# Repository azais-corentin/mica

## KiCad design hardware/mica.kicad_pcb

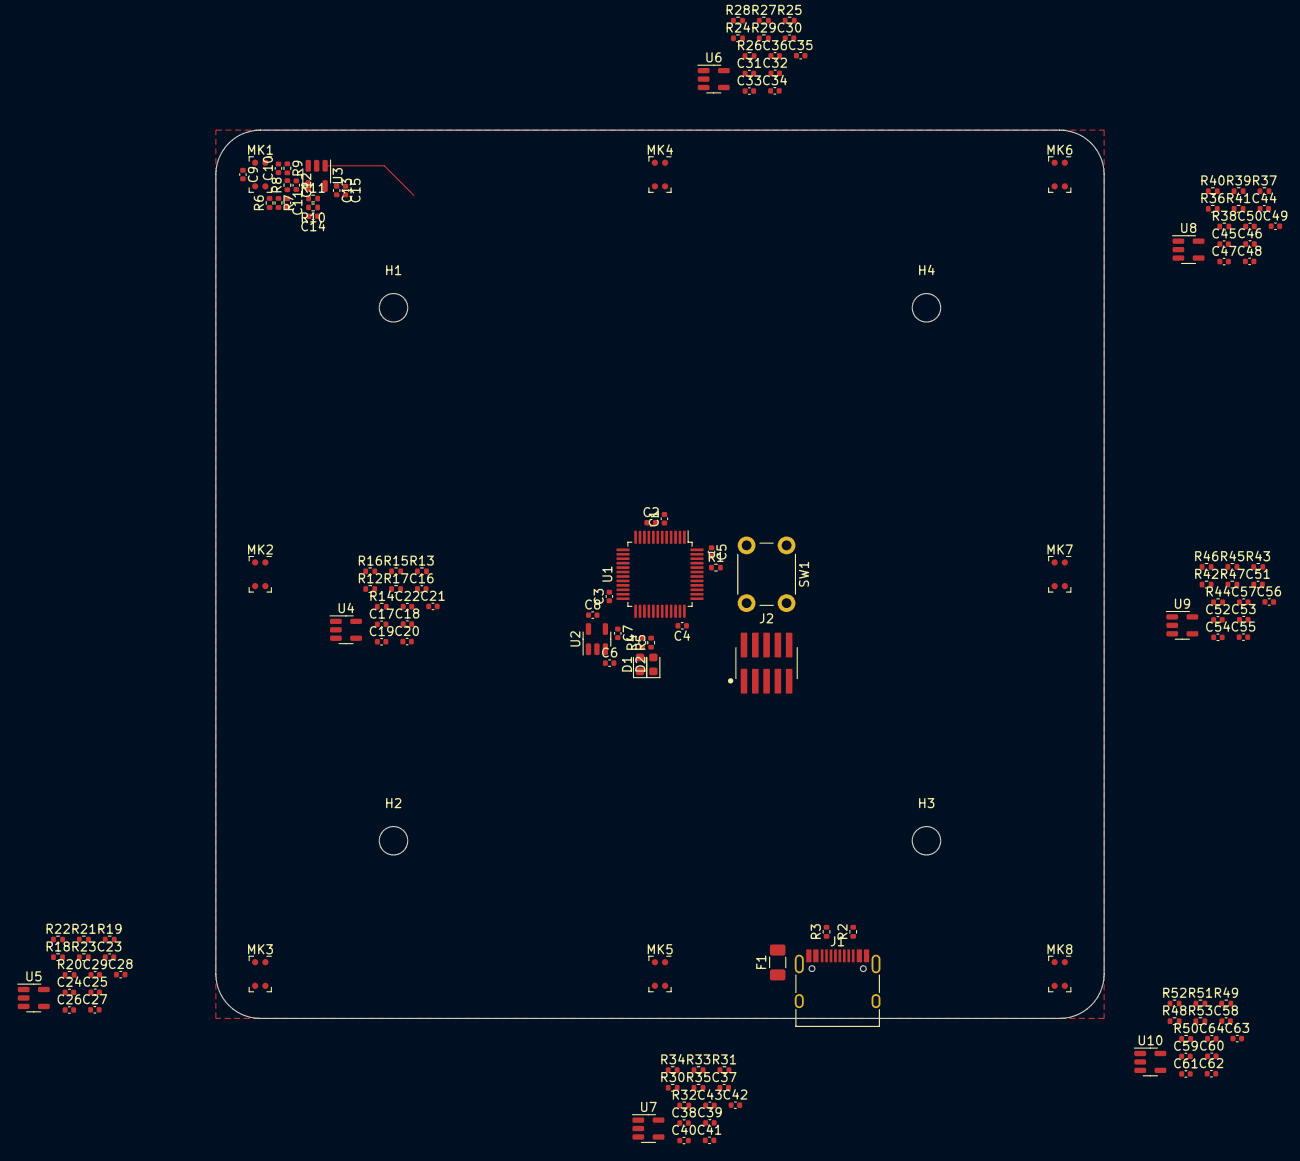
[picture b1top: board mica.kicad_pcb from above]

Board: 2 copper layers, 100.0 x 100.0 mm, 145 parts (0 on the bottom side), 74 nets.

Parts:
C1, C2, C3, C4, C5, C9, C15, C16, C22, C23, C29, C30, C36, C37, C43, C44, C50, C51, C57, C58, C64: 100n; C_0402_1005Metric
C6, C8, C14, C21, C28, C35, C42, C49, C56, C63: 2.2u; C_0402_1005Metric
C7: 470p; C_0402_1005Metric
C10, C17, C24, C31, C38, C45, C52, C59: 1u; C_0402_1005Metric
C11, C12, C18, C19, C25, C26, C32, C33, C39, C40, C46, C47, C53, C54, C60, C61: 47n; C_0402_1005Metric
C13, C20, C27, C34, C41, C48, C55, C62: 10n; C_0402_1005Metric
D1: LED_Red; LED_0603_1608Metric
D2: LED_Green; LED_0603_1608Metric
F1: Polyfuse_Small; Fuse_1206_3216Metric
H1, H2, H3, H4: MountingHole; MountingHole_3.2mm_M3
J1: USB_C_Receptacle_USB2.0; USB_C_Receptacle_HRO_TYPE-C-31-M-12
J2: Conn_ARM_JTAG_SWD_10; Samtec_FTSH-105-01-L-DV-K
MK1, MK2, MK3, MK4, MK5, MK6, MK7, MK8: AP3722AT; AllPower_AP3722AT_3.76x2.24mm
R1: 10k; R_0402_1005Metric
R2, R3: 5.1k; R_0402_1005Metric
R4, R5: 470; R_0402_1005Metric
R6, R7, R8, R12, R13, R14, R18, R19, R20, R24, R25, R26, R30, R31, R32, R36, R37, R38, R42, R43, R44, R48, R49, R50: 1M; R_0402_1005Metric
R9, R15, R21, R27, R33, R39, R45, R51: 1Meg; R_0402_1005Metric
R10, R16, R22, R28, R34, R40, R46, R52: 1k; R_0402_1005Metric
R11, R17, R23, R29, R35, R41, R47, R53: 499k; R_0402_1005Metric
SW1: SW_User; SW_PUSH_6mm
U1: STM32F072C8Tx; LQFP-48_7x7mm_P0.5mm
U2: MIC5205-3.3YM5; SOT-23-5
U3, U4, U5, U6, U7, U8, U9, U10: LMP7715; SOT-23-5

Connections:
+3V3: C2.1, C3.1, C4.1, C5.1, C8.1, C9.1, C13.1, C15.1, C16.1, C20.1, C22.1, C23.1, C27.1, C29.1, C30.1, C34.1, C36.1, C37.1, C41.1, C43.1, C44.1, C48.1, C50.1, C51.1, C55.1, C57.1, C58.1, C62.1, C64.1, J2.1 (VTref), MK1.1 (VDD), MK2.1 (VDD), MK3.1 (VDD), MK4.1 (VDD), MK5.1 (VDD), MK6.1 (VDD), MK7.1 (VDD), MK8.1 (VDD), R6.1, R12.1, R18.1, R24.1, R30.1, R36.1, R42.1, R48.1, SW1.1, U1.1 (VBAT), U1.9 (VDDA), U1.24 (VDD), U1.36 (VDDIO2), U1.48 (VDD), U2.5 (OUT), U3.5 (V+), U4.5 (V+), U5.5 (V+), U6.5 (V+), U7.5 (V+), U8.5 (V+), U9.5 (V+), U10.5 (V+)
/BTN_USER: SW1.2, U1.26 (PB13)
/LED_GREEN: R5.2, U1.28 (PB15)
/LED_RED: R4.2, U1.27 (PB14)
/MIC1: R11.2, U1.14 (PA4), U3.1
/MIC2: R17.2, U1.15 (PA5), U4.1
/MIC3: R23.2, U1.16 (PA6), U5.1
/MIC4: R29.2, U1.13 (PA3), U6.1
/MIC5: R35.2, U1.17 (PA7), U7.1
/MIC6: R41.2, U1.12 (PA2), U8.1
/MIC7: R47.2, U1.11 (PA1), U9.1
/MIC8: R53.2, U1.10 (PA0), U10.1
/NRST: C1.1, J2.10 (~RESET~), U1.7 (NRST)
/SWCLK: J2.4 (SWDCLK/TCK), U1.37 (PA14)
/SWDIO: J2.2 (SWDIO/TMS), U1.34 (PA13)
/USB_D+: J1.A6 (D+), J1.B6 (D+), U1.33 (PA12)
/USB_D-: J1.A7 (D-), J1.B7 (D-), U1.32 (PA11)
GND: C1.2, C2.2, C3.2, C4.2, C5.2, C6.2, C7.2, C8.2, C9.2, C11.2, C12.2, C13.2, C14.2, C15.2, C16.2, C18.2, C19.2, C20.2, C21.2, C22.2, C23.2, C25.2, C26.2, C27.2, C28.2, C29.2, C30.2, C32.2, C33.2, C34.2, C35.2, C36.2, C37.2, C39.2, C40.2, C41.2, C42.2, C43.2, C44.2, C46.2, C47.2, C48.2, C49.2, C50.2, C51.2, C53.2, C54.2, C55.2, C56.2, C57.2, C58.2, C60.2, C61.2, C62.2, C63.2, C64.2, D1.1 (K), D2.1 (K), J1.A1 (GND), J1.A12 (GND), J1.B1 (GND), J1.B12 (GND), J1.S1 (SHIELD), J2.3 (GND), J2.5 (GND), J2.9 (GNDDetect), MK1.2 (GND), MK1.3 (GND), MK2.2 (GND), MK2.3 (GND), MK3.2 (GND), MK3.3 (GND), MK4.2 (GND), MK4.3 (GND), MK5.2 (GND), MK5.3 (GND), MK6.2 (GND), MK6.3 (GND), MK7.2 (GND), MK7.3 (GND), MK8.2 (GND), MK8.3 (GND), R1.2, R2.2, R3.2, R7.2, R13.2, R19.2, R25.2, R31.2, R37.2, R43.2, R49.2, U1.8 (VSSA), U1.23 (VSS), U1.35 (VSS), U1.47 (VSS), U2.2 (GND), U3.2 (V-), U4.2 (V-), U5.2 (V-), U6.2 (V-), U7.2 (V-), U8.2 (V-), U9.2 (V-), U10.2 (V-)
unnamed: C7.1, U2.4 (BP)
unnamed: C10.1, MK1.4 (OUT)
unnamed: C10.2, R9.1, U3.3 (+)
unnamed: C11.1, R6.2, R7.1, R8.1
unnamed: C12.1, R8.2, R9.2
unnamed: C14.1, R10.1
unnamed: C17.1, MK2.4 (OUT)
unnamed: C17.2, R15.1, U4.3 (+)
unnamed: C18.1, R12.2, R13.1, R14.1
unnamed: C19.1, R14.2, R15.2
unnamed: C21.1, R16.1
unnamed: C24.1, MK3.4 (OUT)
unnamed: C24.2, R21.1, U5.3 (+)
unnamed: C25.1, R18.2, R19.1, R20.1
unnamed: C26.1, R20.2, R21.2
unnamed: C28.1, R22.1
unnamed: C31.1, MK4.4 (OUT)
unnamed: C31.2, R27.1, U6.3 (+)
unnamed: C32.1, R24.2, R25.1, R26.1
unnamed: C33.1, R26.2, R27.2
unnamed: C35.1, R28.1
unnamed: C38.1, MK5.4 (OUT)
unnamed: C38.2, R33.1, U7.3 (+)
unnamed: C39.1, R30.2, R31.1, R32.1
unnamed: C40.1, R32.2, R33.2
unnamed: C42.1, R34.1
unnamed: C45.1, MK6.4 (OUT)
unnamed: C45.2, R39.1, U8.3 (+)
unnamed: C46.1, R36.2, R37.1, R38.1
unnamed: C47.1, R38.2, R39.2
unnamed: C49.1, R40.1
unnamed: C52.1, MK7.4 (OUT)
unnamed: C52.2, R45.1, U9.3 (+)
unnamed: C53.1, R42.2, R43.1, R44.1
unnamed: C54.1, R44.2, R45.2
unnamed: C56.1, R46.1
unnamed: C59.1, MK8.4 (OUT)
unnamed: C59.2, R51.1, U10.3 (+)
unnamed: C60.1, R48.2, R49.1, R50.1
unnamed: C61.1, R50.2, R51.2
unnamed: C63.1, R52.1
unnamed: D1.2 (A), R4.1
unnamed: D2.2 (A), R5.1
unnamed: F1.1, J1.A4 (VBUS), J1.A9 (VBUS), J1.B4 (VBUS), J1.B9 (VBUS)
unnamed: J1.A5 (CC1), R3.1
unnamed: J1.B5 (CC2), R2.1
unnamed: R1.1, U1.44 (BOOT0)
unnamed: R10.2, R11.1, U3.4 (-)
unnamed: R16.2, R17.1, U4.4 (-)
unnamed: R22.2, R23.1, U5.4 (-)
unnamed: R28.2, R29.1, U6.4 (-)
unnamed: R34.2, R35.1, U7.4 (-)
unnamed: R40.2, R41.1, U8.4 (-)
unnamed: R46.2, R47.1, U9.4 (-)
unnamed: R52.2, R53.1, U10.4 (-)
VBUS: C6.1, F1.2, U2.1 (IN), U2.3 (EN)

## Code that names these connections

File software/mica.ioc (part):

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Mcu.Name=STM32F072C(8-B)Tx
Mcu.Package=LQFP48
Mcu.UserName=STM32F072C8Tx
PA0.GPIOParameters=GPIO_Label
PA0.GPIO_Label=MIC8
PA0.Mode=IN0
PA0.Signal=ADC_IN0
PA1.GPIOParameters=GPIO_Label
PA1.GPIO_Label=MIC7
PA1.Mode=IN1
PA1.Signal=ADC_IN1
PA11.Mode=Device
PA11.Signal=USB_DM
PA12.Mode=Device
PA12.Signal=USB_DP
PA13.Mode=Serial_Wire
PA13.Signal=SYS_SWDIO
PA14.Mode=Serial_Wire
PA14.Signal=SYS_SWCLK
PA2.GPIOParameters=GPIO_Label
PA2.GPIO_Label=MIC6
PA2.Mode=IN2
PA2.Signal=ADC_IN2
PA3.GPIOParameters=GPIO_Label
PA3.GPIO_Label=MIC4
PA3.Mode=IN3
PA3.Signal=ADC_IN3
PA4.GPIOParameters=GPIO_Label
PA4.GPIO_Label=MIC1
PA4.Mode=IN4
PA4.Signal=ADC_IN4
PA5.GPIOParameters=GPIO_Label
PA5.GPIO_Label=MIC2
PA5.Mode=IN5
PA5.Signal=ADC_IN5
PA6.GPIOParameters=GPIO_Label
PA6.GPIO_Label=MIC3
PA6.Mode=IN6
PA6.Signal=ADC_IN6
PA7.GPIOParameters=GPIO_Label
PA7.GPIO_Label=MIC5
PA7.Mode=IN7
PA7.Signal=ADC_IN7
PB13.GPIOParameters=GPIO_PuPd,GPIO_Label
PB13.GPIO_Label=BTN_PAIR
PB13.GPIO_PuPd=GPIO_PULLDOWN
PB13.Signal=GPIO_Input
PB14.GPIOParameters=GPIO_PuPd,GPIO_Label,GPIO_ModeDefaultOutputPP
PB14.GPIO_Label=LED_RED
PB14.GPIO_ModeDefaultOutputPP=GPIO_MODE_OUTPUT_PP
PB14.GPIO_PuPd=GPIO_PULLDOWN
PB14.Signal=GPIO_Output
PB15.GPIOParameters=GPIO_Label,GPIO_ModeDefaultOutputPP
PB15.GPIO_Label=LED_GREEN
PB15.GPIO_ModeDefaultOutputPP=GPIO_MODE_OUTPUT_PP
PB15.Signal=GPIO_Output
RCC.SYSCLKFreq_VALUE=48000000
RCC.SYSCLKSource=RCC_SYSCLKSOURCE_HSI48
board=custom

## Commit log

2021-02-28 Add MCU, USB, SWD, a button, 2 LEDs, a LDO regulator, 8 microphones with amplification
2021-02-28 Simulate amplification circuit and adjust values accordingly
2021-02-28 Cleanup schematic, connect usb
2021-02-28 Add microphone connections
2021-02-28 Fix all ERC errors
2021-02-28 Assign footprints
2021-02-28 Place button and leds pins
2021-02-28 Assign all footprints
2021-02-28 Remove 4 of the 8 mounting holes
2021-02-28 Place every component except microphones + amplifiers
2021-03-01 Place microphone + amplifier components
